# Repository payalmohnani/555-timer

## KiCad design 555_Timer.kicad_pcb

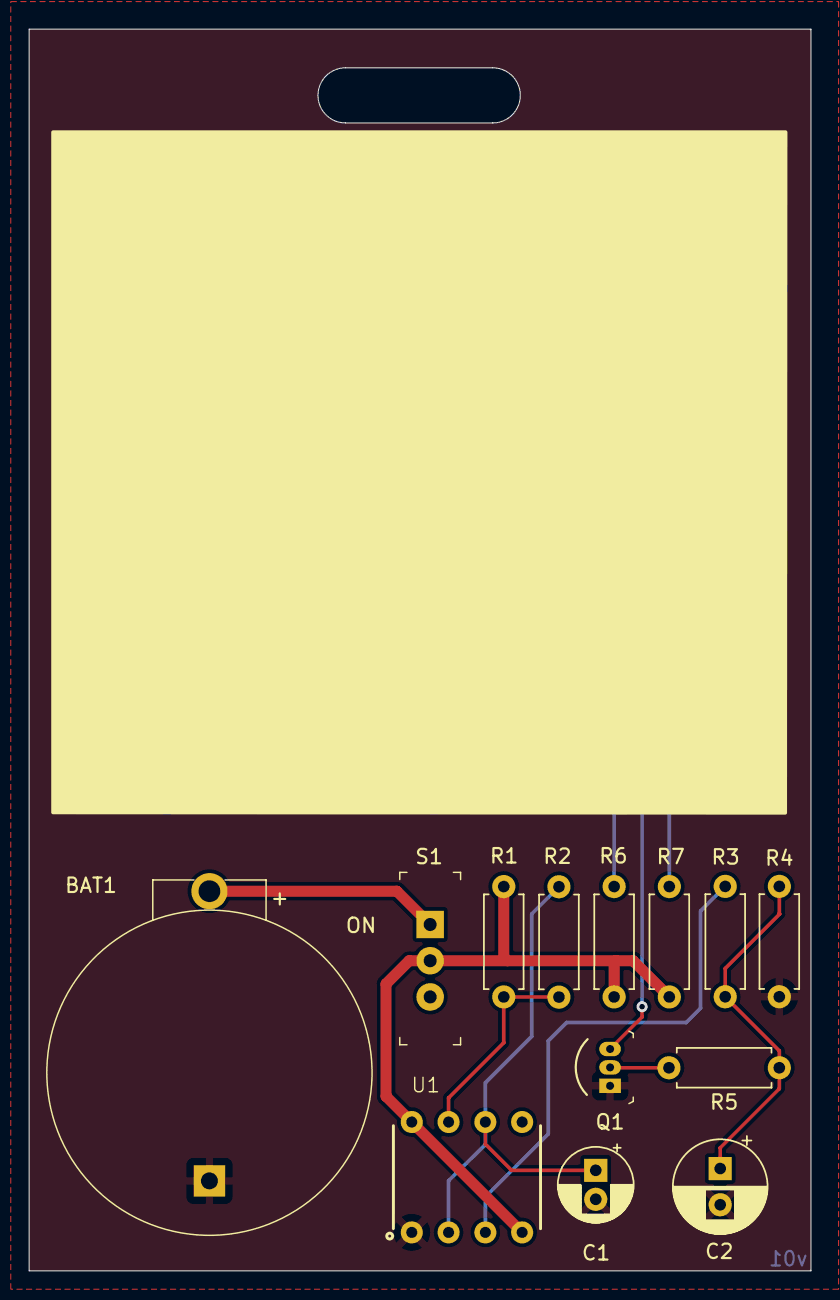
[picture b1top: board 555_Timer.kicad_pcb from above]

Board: 2 copper layers, 54.0 x 85.7 mm, 15 parts (0 on the bottom side), 11 nets.

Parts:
BAT1: BS-7; Battery_Holder_Coin_2032_BS-7
C1: 10uF; CP_Radial_D5.0mm_P2.00mm
C2: 100uF; CP_Radial_D6.3mm_P2.50mm
D1, D2: RED; LED_D3.0mm
Q1: 2N3904; TO-92-3
R1, R3: 22k; R_Axial_DIN0207_L6.3mm_D2.5mm_P7.62mm_Horizontal
R2: 330k; R_Axial_DIN0207_L6.3mm_D2.5mm_P7.62mm_Horizontal
R4: 100k; R_Axial_DIN0207_L6.3mm_D2.5mm_P7.62mm_Horizontal
R5: 10k; R_Axial_DIN0207_L6.3mm_D2.5mm_P7.62mm_Horizontal
R6, R7: 100; R_Axial_DIN0207_L6.3mm_D2.5mm_P7.62mm_Horizontal
S1: EG1218; Switch_Slide_11.6x4mm_EG1218
U1: 7555; ICM7555-PDIP

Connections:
GND: BAT1.Neg, C1.2, C2.2, Q1.1 (E), R4.2, U1.1 (GND)
unnamed: BAT1.Pos, S1.1
unnamed: C2.1, R3.2, R4.1, R5.1
unnamed: D1.2 (A), R6.2
unnamed: D1.1 (K), D2.1 (K), Q1.3 (C)
unnamed: D2.2 (A), R7.2
unnamed: Q1.2 (B), R5.2
unnamed: R1.2, R2.1, U1.7 (DIS)
unnamed: R3.1, U1.3 (OUT)
unnamed: C1.1, R2.2, U1.2 (~TRIG), U1.6 (THRESH)
VCC: R1.1, R6.1, R7.1, S1.2, U1.4 (~RST), U1.8 (VDD)

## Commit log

2023-08-19 Initialized repository

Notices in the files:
555_Timer.kicad_pcb:
creativecommons.org/licenses/by/4.0
License: CC BY 4.0
